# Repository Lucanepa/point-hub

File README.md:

# @openvolley/ledbox-bridge

Mirrors an OpenVolley live match onto a **Tech4Sport LedBox** LED scoreboard.

```
 eScoresheet (Scoreboard)                 LedBox bridge (this service)            Tech4Sport LedBox
        │  computes liveState                       │                                    │
        └── live-state-update (WS) ─▶  LAN relay ──▶  RelaySubscriber                     │
                                                     │  data.liveState                    │
                                                     ▼                                    │
                                            volleyballMapper ── SetSections ──▶ LedboxClient ──gzip/TCP:8889──▶ 📟
```

Small Node service, **no production dependencies** (uses Node 22's built-in global
`WebSocket` for the relay client and `node:net` for the LedBox). It subscribes to the
LAN relay, maps the live match state onto the LedBox `volleyball_matchscore` layout,
and pushes it over TCP with the documented gzip/JSON protocol.

The Point Hub apps (the tablet console, the desktop app for Linux, Windows and macOS) are
downloaded from https://lucanepa.github.io/point-hub/; how each channel is published:
[packaging/README.md](packaging/README.md).

### Runtime on the board

The board's own distro Node is far too old, so the runtime is a tarball install kept
outside the package manager:

    /opt/nodejs -> /opt/nodejs-22.23.2      # symlink; the previous version stays on disk
    /usr/local/bin/node -> /opt/nodejs/bin/node

Upgrading or rolling back is one flip of that symlink plus `systemctl restart
ledbox-bridge`, which is why the unit points at `/opt/nodejs/bin/node` rather than at a
versioned path or at `/usr/bin/node`.

**The board is armhf.** Its kernel is `aarch64` but the userland is 32-bit ARM, so it
needs the `linux-armv7l` tarball — an arm64 build unpacks perfectly and then refuses to
execute, which is a confusing way to find out.

**Node 22 is the last version this board can run.** There is no `linux-armv7l` build of
Node 24 at all; 32-bit ARM was dropped. Node 22 is supported until **2027-04-30**, and
getting past that needs a 64-bit userland on the board, not a newer tarball. Zero
production dependencies is what makes any of this cheap: there is nothing to rebuild
against a new runtime, so an upgrade is a download, a checksum and a symlink.

## Fields shown
points · team short names (in team colour) · sets won · timeouts (**T**) · substitutions (**S**) · serve indicator

## Configure
Copy `.env.example` → `.env`. Every var is optional for the appliance — an empty `.env`
boots a working board on the defaults below (`src/config.js` is the source of truth).

| Var | Default | Notes |
|---|---|---|
| `LEDBOX_HOST` | `172.24.1.1,192.168.5.1` | Comma-separated, tried in turn: the board's own AP, then the bench cable. Pinning ONE address loses the failover — leave it unset unless the board lives elsewhere. |
| `LEDBOX_PORT` | `8889` | |
| `CONTROL_PORT` | `8890` | The console. The QR on the panel and the hall guide point here. |
| `RELAY_URL` / `RELAY_HTTP_URL` | `ws://127.0.0.1:8080` / derived | OpenVolley relay for **Link** mode — only a fallback on the appliance: **Settings ▸ Scorer laptop address** wins (below). The match list (`/api/match/list`) is tried at the relay's own origin first (the standalone `backend/server.js` and the cloud serve HTTP and WS on one port), then on `:5173` of the same host (the desktop app, `frontend/server.js`). Set `RELAY_HTTP_URL` only to pin one URL. |
| `RELAY_DISCOVERY` | `own` | When the configured address does not answer, look for the scorer laptop: one `GET :8080/api/server/status` per address of the networks the board **runs** (its own address ends in `.1` — its Wi-Fi `172.24.1.x` and the bench cable `192.168.5.x`), then `:5173/api/server/status` where 8080 is WS-only, at most 6 s, only on a match-list refresh. Finds both relay families: the standalone `backend/server.js` (`status: 'online'` on 8080) and the desktop app — Tauri, Electron, `frontend/server.js` (`running: true` on 5173). `all` = every private /24 the board is on (a hall network it is a guest on included); `0` = off. A laptop the search found is used for a link only when the operator links a match it listed (each listed match names its laptop, and `POST /api/link` must name a relay the board knows); the Link tab warns when the saved address was silent and another laptop is listing. |
| `BOARD_OPENVOLLEY` | off | `1` = this C0270 serves OpenVolley itself (`pointhub-openvolley.service`, below): the board follows the one **live** match on its own relay (`ws://127.0.0.1:8080`) by itself, every 3 s, as the Point Hub board does for its screen — never over a game scored on the console or a countdown. Written by `provisioning/setup-openvolley-web.sh`. |
| `TLS_CERT`, `TLS_KEY`, `HTTPS_PORT` | empty, empty, `8891` | Both paths set = an HTTPS listener alongside HTTP (wake lock, installable app). Written by `provisioning/setup-console-tls.sh`. |
| `DIRECTUS_URL`, `LIVE_PUBLISH_TOKEN` | empty | Live publishing to wiedisync, below. The same token lets the board fetch the **match sheet** of the game on it (Link tab ▸ This game: Game info + KSCW roster, for the scorer to read off into the eScoresheet) — only with live scoring on, only behind the scorer PIN, and never on a board with no PIN set, because the roster holds birthdates. The copy in `data/gamesheet.json` is deleted once the game is off the board or 3 h past kickoff. Needs the `board` audience in wiedisync's `scorer-roster.js`. |
| `DIRECTUS_URL` (schedule) | `https://directus.kscw.ch` when unset | Where the **season's home games** come from (`GET /api/schedule`, the console's "start from the schedule" list). A public, token-free read of `/items/games`, so it works without `LIVE_PUBLISH_TOKEN`. The board downloads every remaining home game whenever it has an uplink (at boot, every 30 min, retrying 1→5 min after a failure, and as soon as NTP syncs) and keeps them in `data/schedule.json`, so a hall with no uplink still gets the list — marked stale. No copy at all = a plain "type the names instead" message, never an error. |
| `SCHEDULE_HALLS` | empty (every hall) | Comma list of hall names, e.g. `KWI A,KWI B`: only games in those halls are offered (and prepared automatically). Case-insensitive. |
| `SCHEDULE_SYNC` | on | `0` = no background download and no automatic pre-match; the schedule is then only fetched when a console asks for it. |
| `UPLINK_WATCH` | on | Watch the board's internet and offer the **hall Wi-Fi login** (below). `0` = no background probe. `UPLINK_PROBE_URL` / `UPLINK_PORTAL_URL` point it at a fake portal for testing; they default to Android's `generate_204` and `https://login.pwlan.ch`. |
| `CABLE_TRUST`, `CABLE_ADDRESS`, `CABLE_SUBNET` | on, `192.168.5.1`, `192.168.5.0/24` | **A tablet on the cable is never asked for the scorer PIN** (owner decision 2026-10-22: the cable is a direct, physical connection). A request that arrived on `CABLE_ADDRESS` (the board's eth0) from an address inside `CABLE_SUBNET` (the board itself excluded) passes every PIN gate, on http and https alike, is never counted by the brute-force lock-out, and is told so: `/api/status` answers it `pinRequired:false, pinTrust:"cable"`, `/api/settings` `pinSet:false` (so the tablet app's start-up PIN screen stays down), with `pinConfigured` saying whether the board has a PIN at all. Decided from the TCP connection only — no header, query or `X-Forwarded-For` counts. Everyone else (the board's Wi-Fi `172.24.1.x`, the hall uplink, the tailnet, loopback, a Wi-Fi client aiming at `192.168.5.1`) is gated as before. `CABLE_TRUST=0` switches it off; a malformed address or subnet switches it off too and says so at boot. See `src/cableTrust.js`, `test/cable-trust-selftest.mjs`. |
| `STATE_DIR` | empty (the checkout) | Where everything the appliance **writes** lives: `settings.json` (the scorer PIN with it), `data/` (match history, the resume slot, logs, the schedule copy, the upload ledger, the hall-login stamp, the match-sheet copy) and the boot markers `.sport-switch` and `data/.running`. Empty keeps the paths every board has always used. A board with a **read-only root** sets it to a directory on its persistent data partition (e.g. `STATE_DIR=/data/ledbox`, absolute): on an overlay root anything written elsewhere is lost at the next power cut. Not covered by it, because they belong to the OS or the panel firmware: `/etc/NetworkManager/system-connections`, `/var/lib/tailscale`, the TLS cert dir, the fake-hwclock / timesyncd stamps, and the firmware's own `setting.ini` and `PANEL_OFF` under `/home/pi/ledbox` — a read-only root bind-mounts those itself. A state dir that cannot be written is logged at boot at error level; the board still scores, from memory. `firmware/ledbox-watchdog.sh` reads the same `STATE_DIR` from this `.env`. `test/state-dir-selftest.mjs` fails on any new write path until it is classified. |
| `LOG_LEVEL` | `info` | `debug` \| `info` \| `warn` \| `error`; `DEBUG=1` is shorthand for `debug`. |
| `MOCK` | off | `1` = in-process mock LedBox, no hardware. |
| `MATCH_ID` | — | Only the headless `src/bridge.js` needs it; the appliance picks matches in the UI. It is the match's **seed key** (`match_…`, the `id` in the relay's `/api/match/list`, also in the scorer's QR code) — the relay keys rooms by it. The scorer's local numeric match id receives nothing. |

`LEDBOX_LAYOUT` is read by the headless bridge only — the appliance takes its layouts from the
active sport (`src/sports.js`).

### Publishing the board to wiedisync (`/live`)
Optional. Set **both** of these and the appliance mirrors every score change to the
club's Directus, so members can follow the match at `wiedisync.kscw.ch/live`:

| Var | Value |
|---|---|
| `DIRECTUS_URL` | `https://directus.kscw.ch` (dev: `https://directus-dev.kscw.ch`) |
| `LIVE_PUBLISH_TOKEN` | static token of `ledbox-board@kscw.ch` — its policy can touch `live_scores` and nothing else |
| `LIVE_CHANNEL` | the board's own row. Unset: `kscw` on the club's first board (host `ledbox-c0270`, or a generic host name such as `raspberrypi`), the host name on any other board (`ledbox-court2` → `ledbox-court2`), so a second board on defaults never overwrites the first one's row. Set it explicitly on every board; it must match the channel the board's token is allowed to write. Never `game-…` (ignored, with a warning). |

Leave either blank and the publisher is a **no-op** — the board behaves exactly as
it does without it.

**Two rows when the game is known.** Every match goes to the board's own row, team A =
the LEFT side, exactly as before. When the board knows *which game* it is showing — started
from the schedule (the console's tap or the automatic pre-match), or a linked OpenVolley
match whose match number (`game_n`) is in the season copy — it also writes wiedisync's
per-game row `game-<games.id>`, the row the game modal's *Watch live* and the result
entry's prefill read (`src/liveFixture.js`):

| | board row (`LIVE_CHANNEL`) | game row (`game-<id>`) |
|---|---|---|
| team A | whoever stands on the left (swaps at every change of ends) | the schedule's **home** team, all match |
| `set_results` | by side, swapped with the ends | by team, home first |
| written | every change | from the first point (not the 0-0 pre-match), when the names on the board tell home from away |
| extra columns | — | `game_id`, `source: 'board:<channel>'` |

Who is home is read from the names on the board against the schedule's; when they fit both
ways, a board set up from the schedule (home on the left) goes by `ends_swapped`. When the
names fit neither way (retyped, or the next game already up) **no** game row is written:
a missing prefill is a nuisance, a swapped one is a wrong result sent to Volleymanager.
The finished match's `live_history` row stays on the board's channel and, when the game is
known, carries `game_id` and is home/away too (a Directus that refuses `game_id` gets the
row again without it).

- **Linked OpenVolley matches.** OpenVolley publishes to the LAN relay and its own cloud,
  never to wiedisync, so the board mirroring it is the only writer of that game row — once
  per change, like the board row. A linked match is never filed under the game the board was
  set up for before the link; only its own match number counts.
- **KSCW vs KSCW.** A derby is two `games` rows (one per team, `type` home / away). The
  season copy fetches `type: home` only, so the game is published once, under the **home**
  team's row id; the away team's copy gets nothing (wiedisync resolves the sibling).
- **Refused.** Until wiedisync lets the board's token write `game-*` rows, Directus refuses
  them: the board says so once in the log, leaves that row alone for 30 min and keeps
  publishing its own row as before. A row nobody has written yet answers a PATCH with 403,
  so 403/404 mean "create it".
- **Phone live scoring** writes the same `game-<id>` rows; the board's write is
  unconditional, so while the board publishes a game, the board wins. Every failure inside it (outage, bad token, slow network) is
swallowed, so it can never affect scoring. These are deliberately distinct from
`RELAY_URL`, which is the LAN relay the board *subscribes* to.

A failed live write is retried with the latest score, backing off and bounded; a new
point during a backoff goes out after the normal debounce instead of waiting it out. A
4xx is not retried. A finished match's history row is resent only when it provably
never reached Directus, so a timeout can lose that row but never duplicate it.

⚠️ Prod and dev have **different** tokens, and the dev one is replaced by the
nightly prod clone. Collection, permissions and setup:
`wiedisync/src/modules/live/DIRECTUS-SETUP.md`.

The publisher sends the active sport, so the app renders the right board — the
sport is fixed at boot (switching it restarts the appliance). Note that
`BasketballSource` carries team fouls in `subs_a`/`subs_b`; `livePush` translates
that to explicit `fouls_a`/`fouls_b` on the wire.

## Test / run
```bash
# everything: source rules + every test/*-selftest.mjs (no network, no hardware; the panel
# driver tests — test:panel — need Linux for flock/pgrep and skip themselves elsewhere)
npm test

# unit test: mapper → client → mock LedBox (no deps, no hardware) — the on-Pi smoke test
npm run test:mapper

# integration tests: mock relay → bridge / appliance → mock LedBox (needs devDeps)
npm install && npm run test:relay

# end to end against the CURRENT OpenVolley relays (manual: needs an OpenVolley checkout with
# backend/ and frontend/ node_modules). Runs one match against each relay family on free ports —
# backend/server.js --local, frontend/server.js (the desktop Node relay, same core as Electron) and
# the Tauri relay (--server-only, when a build exists; skipped otherwise) — and drives the real
# appliance through the network search (the real /api/server/status), Settings, /api/matches and
# /api/link, asserts the panel at every step, exits 1 on any miss
npm run test:e2e                                   # OPENVOLLEY_DIR defaults to ../openvolley/escoresheet
E2E_RELAYS=backend,desktop npm run test:e2e        # a subset; OPENVOLLEY_TAURI_BIN = a Tauri build

# run for real against the built-in mock (no hardware):
MOCK=1 MATCH_ID=match_1759750000000_ab12cd RELAY_URL=ws://127.0.0.1:8080 node src/bridge.js

# run against a real LedBox (MATCH_ID = the seed key, see Configure):
MATCH_ID=match_1759750000000_ab12cd LEDBOX_HOST=172.24.1.1 node src/bridge.js
```

## OpenVolley on the board (C0270)
Score in OpenVolley on a **tablet or a phone**, with no laptop and no internet: the board serves
OpenVolley's own web app and relay (`frontend/server.js`, unchanged, HTTP **:5173**, WS **:8080**)
and follows the match by itself. Design and the per-device table:
[`docs/openvolley-link-DESIGN.md`](docs/openvolley-link-DESIGN.md). The Point Hub DIY board does
not need it: OpenVolley runs on its own screen.

| Device on `ledbox_C0270` (or the cable) | Do |
|---|---|
| any browser (phone, tablet, iPad, iPhone, PC) | open `http://172.24.1.1:5173` (cable: `http://192.168.5.1:5173`) |
| OpenVolley Android app | Options ▸ Server ▸ Change server ▸ Local ▸ `172.24.1.1` |
| PC with the OpenVolley desktop app | as before: its own relay, linked from the Link tab |

```bash
tools/build-openvolley-web.sh 3.0.20    # on a laptop: dist-openvolley/openvolley-web-3.0.20.tar.gz
./deploy-board.sh                       # ships it to /home/pi/openvolley-web/<version>, `current` flips
# once, on the board:
sudo bash ledbox-bridge/provisioning/setup-openvolley-web.sh            # --check
sudo bash ledbox-bridge/provisioning/setup-openvolley-web.sh --apply    # service + firewall defaults + BOARD_OPENVOLLEY=1
sudo bash ledbox-bridge/provisioning/install-firewall.sh                # opens 5173/8080 on the AP + cable
sudo bash ledbox-bridge/provisioning/install-firewall.sh --commit       # after a phone opened :5173
```
Each OpenVolley release: build its bundle and deploy again (the last 3 stay on the board; roll
back by pointing `current` at the old one and `sudo systemctl restart pointhub-openvolley`).
Tested by `OPENVOLLEY_WEB_DIR=<unpacked bundle> E2E_RELAYS=board npm run test:e2e`.

## Appliance — web control UI (manual + link)
Instead of the headless bridge, run the **appliance**: a phone-friendly control page
served by the Pi (`CONTROL_PORT`, default 8890) with two modes — **Manual** (drive the
board by hand: names, ±points, sets, timeouts, subs, serve, swap) and **Link** (list LAN
matches from the relay and mirror one live). Cloud/Supabase source is a stub.

- **Scorer laptop** — the relay Link mode reads from is the scorer's OpenVolley laptop, whose
  address changes from hall to hall. **Settings ▸ Scorer laptop address** takes `host[:port]`
  (`172.24.1.23`, `172.24.1.23:9000`; port 8080 when left out; a pasted `ws://…`/`http://…` URL is
  fine, `wss://host` for a relay on the internet), refused with the reason when malformed and kept
  with the other settings. **Check** saves it and asks the laptop for its matches. Empty (the
  default) = `RELAY_URL` if set, else the board itself, and when nothing answers the board searches
  its own Wi-Fi and cable for a laptop (`RELAY_DISCOVERY`, `src/relayAddress.js`). The Link tab
  names the laptop that answered — or the address it tried and why it failed — and a link
  subscribes to the relay that listed the match. A match is listed by the relay only once the
  scorer has synced it (today's relays also want the referee connection on).
- **End of a linked match** — when the scorer ends the match (`match_status: 'ended'` in the live
  state), the panel shows the result screen (winner, sets; the clock on a board without
  `kscw_result`); an undo of the end brings the score back. When the scorer deletes the match
  (`match-deleted`), the board unlinks (mode `idle`) and holds the clock — or keeps the result if
  it is already up — instead of freezing the last score. Relay `error` frames are logged.
- **Breaks of a linked match** — with one scorer at the OpenVolley laptop, the board runs the
  breaks itself, on the same break screen, clock and horn as a console tap: the scorer's timeout
  puts up **TIME OUT** with the calling team (the one whose timeout count went up), a set end the
  **INTERVAL** with the set score, each for the length in Settings ▸ Countdowns. Each is timed from
  the moment the board sees it, never from the laptop's `*_started_at`. The laptop's end takes it
  down — silently when the scorer stopped it early, with the horn when it lands within 3 s of the
  board's zero — and when that end never comes (a link drop), the board's own zero ends it. A
  timeout is on while `timeout_active` is; OpenVolley sets `set_interval_active` on the set_end
  frame only, so the next set's line-ups do not end the interval, and End interval, Start set, an
  undo or a rally in the new set do. A console tap wins: a skip stays skipped, a countdown the
  operator starts over it is theirs, and nothing starts over Show clock or with Settings ▸ Show on
  timeout / Show on set interval off. A match end ends any break before the result goes up.
  Indoor volleyball only (`sports.js` `linkBreaks`); beach, basketball and simple links are as
  before.
- **Live-state order** — OpenVolley numbers every live state it pushes (`_seq`, within the
  `_session` of one scoring page; a reload starts again at 1). A state older than the newest one
  the board has taken is dropped (`src/relaySubscriber.js`), so the relay's replay after a
  reconnect can neither roll the score back nor start a break twice.
- **Scorer PIN — mandatory** — the board's AP passphrase is on the panel, so a real boot requires a
  scorer PIN. A board that has none yet (every board on the day this shipped) refuses writes from
  its Wi-Fi with *"This board has no scorer PIN yet — set one in Settings before scoring."* and the
  console shows **Set a scorer PIN** in front of everything (PIN typed twice) until someone sets
  one — that one save needs no PIN. In the tablet app the console comes to the front by itself to
  do it; the app's own screens can only type a PIN. A tablet on the **cable** is never blocked
  (`CABLE_TRUST`) and only reminded. The PIN can be changed (with the current one), not removed.
  Lost PIN: on the board, remove `scorerPin` from `settings.json` (in `STATE_DIR`) and restart the
  bridge — it is back in the setup, and the next operator sets a new one. Keep the PIN in the vault
  and on the coaches' sheet, not on the public hall card.
- **Which board** — `/api/status.board` names the board beside `fontsize`: `id` (settings.json
  `boardId`, set on the board only and never through the API since tablets pair against it, else
  the hostname), `idSource`, `label` (`boardLabel`, e.g. "Court 2", else the id) and `caps`:
  `sports`, `panel` `{ width, height, source }` read from the firmware's `setting.ini` [DISPLAY]
  (192×64 when absent), `renderer` `{ kind: 'vendor' | 'openscore', version, device }` from the
  board's own Init reply (null before the first handshake). Nothing existing was renamed.

- **Undo** — one button beside the set strip takes back the last action, whatever it was
  (point, timeout, sub, swap, next set, reset), up to 30 steps; it reads what it will undo
  (`Undo · Point KSCW`) and the history log follows it. A second `+` for a team that has
  already won the set is refused instead of scoring (`set-closed`).
- **Schedule and pre-match** — the Link tab lists today's home games and the rest of the season
  (`GET /api/schedule?range=season`: `{ ok, fetchedAt, stale, today, upcoming:[{ date, games }] }`,
  served from the copy on the board's card). Tapping one sets it up behind the wall clock until
  the warm-up ends. With **Settings ▸ Prepare home games automatically** (on by default) the
  board does that tap itself 60 minutes before a game of its sport — once the clock is synced,
  never over a match in progress or a running countdown, never again for a game the scorer
  dismissed that day, and only when it is the one home game of its sport that day: with two or
  more it prepares none and the scorer picks one on the Link tab (`src/autoPrepare.js`).
- **Hall internet** — at a hall whose Wi-Fi has a login page (the KWI hall's `Free_WLAN_KTZH`,
  a Swisscom Public WLAN), live scoring stops until the board is logged in, and the board has no
  browser to do it in. **Settings ▸ Hall internet** does it from the console: the scorer's mobile
  number, then the SMS code; the board walks the portal itself (`src/hallLogin.js`) and stays
  logged in about 24 h. The Game tab shows a banner only while the login page is in the way. The
  number is asked for every time and never stored or logged — the scorer changes every match.
  `GET /api/uplink` → `{ status: online|portal|offline|checking, portal, ssid, validUntil,
  loggedInAt, step: idle|code }`; `POST /api/uplink/check`, `/api/uplink/login { phone }` →
  `{ ok, step:'code' }`, `/api/uplink/code { code }` → `{ ok, status:'online', validUntil }`
  (PIN-gated, always 200 with `{ ok:false, error }` in plain words on a refusal). Both login
  calls also carry the console's `epochMs`: the board has no RTC, and if its clock is behind the
  portal's (freshly renewed) certificate the HTTPS login fails, so it adopts the console's time —
  even mid-match — and tries once more. `/api/status` carries `uplink: { status, validUntil }`. The Wi-Fi itself is set up by
  `provisioning/setup-wlan1-client.sh --hall`, which also carries the DNS fix that network needs.
  When the scripted login cannot get through (the portal slow or changed), **Open the login page**
  shows the hall's own page on the tablet, fetched by the board (`src/portalProxy.js`, under
  `/hall-login/`), so it is still the board that logs in: `POST /api/uplink/portal` (PIN) opens it
  for that tablet for ten minutes, its scripts run sandboxed away from the console's storage, and
  its cookies stay on the board. An offline `/api/uplink` also names the Wi-Fi and says `why`.
- **Panel test** — **Diagnostics ▸ Panel test** is the volunteer's self-check of the LED hardware,
  on the glass: **Show test screen** puts up `kscw_test` (`layouts/36_kscw_test.xml`), which
  numbers the C0270's three 64×64 modules **1 | 2 | 3** from the left, frames each one in white and
  draws red, green, blue and white bars under each number. A dark module, a frame with a gap, a
  missing bar or numbers out of order point at that module or its ribbon. **Test horn** sounds the
  horn once — unless Settings ▸ Horn when a countdown ends is off, which it then says. Both are
  refused during a match (the scoreboard showing a started, unfinished match, or a linked match)
  and during a countdown. The test screen goes back to exactly what was there (the held clock,
  the crest, the scoreboard, the result) after 20 s, on **Back to normal now**, and the moment
  anything else wants the panel (a point, a countdown, Show clock…); a reconnect, the layout guard
  and the idle ticker each take down a test screen with no test behind it, so nothing can leave the
  panel on it. `POST /api/paneltest { action: 'start' | 'stop' | 'horn', seconds? }` (PIN; 409 with
  the reason when refused); `/api/status` carries `ledbox.test: { endsAt, remainingMs } | null`.
  The layout ships with `deploy-board.sh` like every `*_kscw_*.xml`. `npm run test:paneltest`.
- **Finished sets on the interval screen** — **Settings ▸ Display ▸ Finished sets on the interval
  screen** (off by default) puts each finished set (`25-21  23-25`, two to a line, the left team's
  score first) under the clock on the set-interval screen, in two new `kscw_break` sections,
  `hist1`/`hist2`. Only for matches scored on the board: a linked OpenVolley match sends no set
  scores. Written apart from the break screen itself, so a board whose `kscw_break` predates the
  two sections (layout not deployed, or the panel not restarted since) loses only these lines —
  refused once per connection and logged, the interval screen painted as before. Timeouts and the
  warm-up show none. A deliberately static line rather than a rotating carousel: the hall and the
  referees read the interval clock, and frames that change underneath it are motion for the camera.
  `npm run test:interval`.
- **Portrait works** — a phone held upright gets a stacked layout (left team on top) instead
  of a "rotate" wall; a dismissible tip still suggests landscape.
- **Theme** — **Settings ▸ Theme**: Light (the default), Dark, or E-ink — greyscale, paper white
  and ink black, for a phone courtside in full sun. Per screen, never on the board:
  `localStorage.theme`, shown as `<html data-theme="dark|eink">`, set by a boot script at the top
  of `web/index.html` before the first paint; `/logs` follows it. The looks are token sets on
  `:root`; e-ink carries what colour alone used to (which team, a limit, the chosen tab) as fill
  versus outline, dashes and underlines, and drops shadows and motion. `npm run test:theme`.
- **Inside the Android app** (`android/`, contract `android/BRIDGE.md`) — the app shows this console
  in a kiosk WebView. From app 1.1.0 it draws the header, the tab bar and the Game tab natively, and
  the console runs in *embed mode* under the app's tab bar for Link, History, Diagnostics and
  Settings, with the scorer PIN and the theme shared with the app (BRIDGE.md, "Native Game tab";
  `npm run test:embed`).
- **The tablet's app** — with `TLS_CERT`/`TLS_KEY` set (`provisioning/setup-console-tls.sh`),
  `/api/status` carries `httpsOrigin` (the cert's first DNS name + `HTTPS_PORT`; `null` without
  TLS or once the cert has expired), and a console opened on `http://172.24.1.1:8890` moves itself
  there when it can reach it — between matches, never mid-match (a *Switch* bar until then). From
  the https address Chrome offers **Install app** (`web/manifest.webmanifest`): full screen,
  landscape, screen kept awake from launch, no tap-to-start.
  - **Install it once with internet.** Chrome on Android builds the app (a WebAPK) through
    Google's servers; on the board's own Wi-Fi, which has none, the install can fail or fall back
    to a plain shortcut. Install while the tablet has internet *and* reaches the board by its
    tailnet name (Tailscale on the tablet, or the hall Wi-Fi when the board shares it), then launch
    it once on the board's Wi-Fi to check it opens full screen, landscape, and stays lit.
  - **The app is bound to that exact origin.** Renaming the tailnet node or changing
    `HTTPS_PORT` means uninstalling and installing it again.
  - **The first move to https asks for the PIN again.** Browser storage is per origin, so the
    https console starts without what the http one remembered (scorer PIN, keep-awake, the
    dismissed rotate tip). Once only.
  - **If the app opens on "The board didn't answer here"**, the tablet could not look the name up
    or reach it (Private DNS or Chrome Secure DNS set to a provider, mobile data carrying DNS, the
    tablet on another network). That page is `web/sw.js` — a service worker that caches nothing
    and only answers a page load that failed — and it links `http://172.24.1.1:8890`, which still
    works. A lapsed certificate shows Chrome's own warning page instead (no worker runs there):
    use the same plain address.
```bash
npm run appliance                 # open http://<pi-ip>:8890  (or http://openvolley:8890 over Tailscale)
MOCK=1 npm run appliance          # in-process mock LedBox, no hardware
npm run test:appliance            # API → source → mapper → mock LedBox integration test
```
Architecture and the remaining phases (cloud source, auth, persistence) are in
[`DESIGN-appliance.md`](./DESIGN-appliance.md).

## Logs — `/logs`
Everything the appliance does is recorded to one structured log: board writes and layout
switches, every scored action, source and relay lifecycle, settings changes, live-scoring
publishes, and the browser's own errors. Open **`http://<board-ip>:8890/logs`** (linked from
Settings ▸ Diagnostics) for a live tail with level/scope filters, search, download and a
runtime verbosity switch.

```bash
LOG_LEVEL=debug npm run appliance   # boot verbose (DEBUG=1 still works); also switchable at /logs
curl http://<board-ip>:8890/api/logs/export > board.jsonl  # the whole trail, for a bug report
journalctl -u ledbox-bridge -f                             # unchanged — everything still mirrors to stdout
```

Persisted to `data/logs/*.jsonl`, rotated at 5 MB × 3 files (**15 MB ceiling**, SD-card
friendly). The scorer PIN, the Directus token and any phone number are redacted before anything
is written.
Design notes: [`docs/logging-DESIGN.md`](./docs/logging-DESIGN.md).

## Livestream overlay — `/overlay` and `/api/overlay.json`
The board serves the score for a livestream, so nobody has to type it into the streaming software
a second time. Read-only and open (no PIN for a GET), and it carries nothing the club's public
`/live` page does not already show: team names, colours, sets, points, who serves, the finished
sets, and the countdown the panel is showing (time-out, interval, warm-up). Built from the same row
livePush publishes (`src/overlay.js` on top of `toRow`), so no player, referee or roster data can
reach it.

- **OBS** — Sources ▸ + ▸ *Browser*, URL `http://<board>:8890/overlay`, width **1920**, height
  **1080**. The page is transparent; only the scorebug in one corner is drawn. Options in the URL:
  `?corner=tl|tr|bl|br` (default `tl`), `?scale=1.5` (0.5–3), `?history=0` (hide the finished
  sets), `?preview=1` (a chequered backdrop, to judge it in an ordinary browser). The bug is hidden
  while the board has no match on it.
- **vMix** — Data Sources ▸ + ▸ *JSON*, URL `http://<board>:8890/api/overlay.json`, then bind a
  title's fields to its columns. One flat object, every key always present (blank or `0` when it
  does not apply):

  | Key | |
  |---|---|
  | `team_a`, `team_b` | the short code as the panel shows it (else the name), capitals |
  | `team_a_name`, `team_b_name`, `team_a_color`, `team_b_color` | full name; `#rrggbb` |
  | `points_a/b`, `sets_a/b`, `timeouts_a/b`, `fouls_a/b` | numbers (fouls: basketball) |
  | `serving` | `a`, `b` or empty |
  | `period`, `period_label` | `2`, `SET 2` (basketball `Q2`, `OT1`) |
  | `status` | `idle` (no match), `live`, `final` |
  | `set_scores`, `set1_a` … `set5_b` | `25-21  23-25`, and each set on its own |
  | `break`, `break_team`, `break_seconds`, `break_clock` | `TIME OUT`, `KSCW`, `23`, `0:23` |

  Teams are A and B as `/live` has them: on the board's own scoring, A is the team on the panel's
  left (a change of ends swaps them, as on the panel); a linked OpenVolley match keeps A fixed.
- **Live updates** — `/overlay` listens to `GET /api/overlay/stream` (Server-Sent Events: a frame on
  connect, then one per change) and polls the JSON every 3 s while the stream is down. At most 8
  streams at once (a 503 past that; the page then polls). Both endpoints answer cross-origin reads
  (`Access-Control-Allow-Origin: *`) — unlike every other read here — so a producer's own graphics
  page can use them. Overlay reads do not count as someone at the console: the panel's "Join WiFi /
  Open UI" QR codes are not hidden by a streaming PC left running.
- **Reaching the board** — the streaming laptop needs the internet, and the board's own Wi-Fi
  (`ledbox_C0270`) has none; a public hall Wi-Fi usually keeps its clients apart, so a laptop there
  rarely reaches the board either. What works: the board's **tailnet name** with Tailscale on the
  laptop; a **cable** to the board's ethernet (`http://192.168.5.1:8890/overlay`) while the laptop's
  Wi-Fi carries the stream; or the laptop on `ledbox_C0270` with its internet from a phone over
  **USB tethering**. A producer who cannot reach the board at all needs a page on kscw.ch reading
  the public `live_scores` row instead (the same read `/live` makes) — not built here.
- **Delay** — the overlay follows the board, which follows the scorer: a few seconds behind the
  rally. To line it up with the picture, delay the camera by the same amount (OBS: the camera's
  *Render Delay* filter, and the same *Sync Offset* on its audio).
- Where the stream goes (and who processes the players' images there) is the club's decision; the
  overlay itself adds team names and the score only. `npm run test:overlay`.

## Deploy on the Pi (systemd)
```bash
# on the Pi (reachable as `ssh openvolley`):
cd ~/ledbox-bridge
cp .env.example .env && nano .env        # optional — the defaults drive the board (see Configure)
sudo cp systemd/ledbox-bridge.service /etc/systemd/system/
sudo systemctl daemon-reload && sudo systemctl enable --now ledbox-bridge
journalctl -u ledbox-bridge -f
```

## Status / open items
- **Validated:** mapper + protocol + TCP client + relay subscriber, on the Pi 5 against
  mocks (`npm test`).
- **Wired (app side):** the Scoreboard now also pushes its computed live-state over the
  LAN relay as a `live-state-update` message (`Scoreboard.jsx`); `server.js` merges it
  into the match store and fans it out to subscribers, and the bridge consumes it.
  Verified with mocks — still needs a live end-to-end run with a real scoreboard + relay.
- **Pending (hardware):** confirm the real LedBox's `volleyball_matchscore` section
  names — especially `sub1`/`sub2` and the team-name fields — and upload a custom
  layout via TCP :12345 if they differ.

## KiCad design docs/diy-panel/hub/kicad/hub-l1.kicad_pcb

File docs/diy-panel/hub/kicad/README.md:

# Hub board L1 in KiCad

`build_pcb.py` turns `../layout.json` (the paper-checked positions from `../gen.mjs`) into
`hub-l1.kicad_pcb`: standard KiCad 9 footprints, a net on every pad, and a two-layer route from a
small grid router in the same script (0.3 mm tracks, 0.2 mm clearance, 0.6/0.3 mm vias). Nothing
is drawn by hand, so a change to the paper drawing is one `./make.sh` away from new Gerbers.

```bash
./make.sh        # layout.json → board → DRC (must be clean) → img/*.png → hub-l1-jlcpcb.zip
```

The board opens in KiCad as usual (`hub-l1.kicad_pro`). There is no schematic: the connections
are the table on page 3 of `../hub-level1.pdf`, and `build_pcb.py` (`net_for`, `RES_NETS`) is the
netlist.

## Ordering at JLCPCB

Upload `hub-l1-jlcpcb.zip`. Settings: 2 layers, 90 × 60 mm, 1.6 mm, quantity 5, HASL lead-free,
any colour, no assembly. Only PCB, no stencil.

## Parts to solder (all through-hole)

| Ref | Part | Qty |
|---|---|---|
| J1 | JST-XH socket, top entry, 6-pin (B6B-XH-A) | 1 |
| J2–J6, J8–J10 | JST-XH socket, 4-pin (B4B-XH-A) | 8 |
| J7, J11 | JST-XH socket, 2-pin (B2B-XH-A) | 2 |
| U1 | female header 2.54 mm, 1 × 10 and 2 × 10, 8.5 mm tall | 1 + 1 |
| U2 | female header 2.54 mm, 1 × 4, 8.5 mm tall | 1 |
| R1 / R2, R5 / R3, R4, R6, R7 | ¼ W axial: 10k / 150 / 47 | 1 / 2 / 4 |
| H1–H4 | M2.5 standoffs + screws | 4 |

Plus the matching pre-crimped JST-XH pigtails, and 4 straight male pins for the DS3231.

The JST-XH sockets go in with the latch side as printed on the silkscreen outline. The MCP23017
sits label side up (VCC on the square pad of the single row), the DS3231 chip side up on its four
pass-through pins.

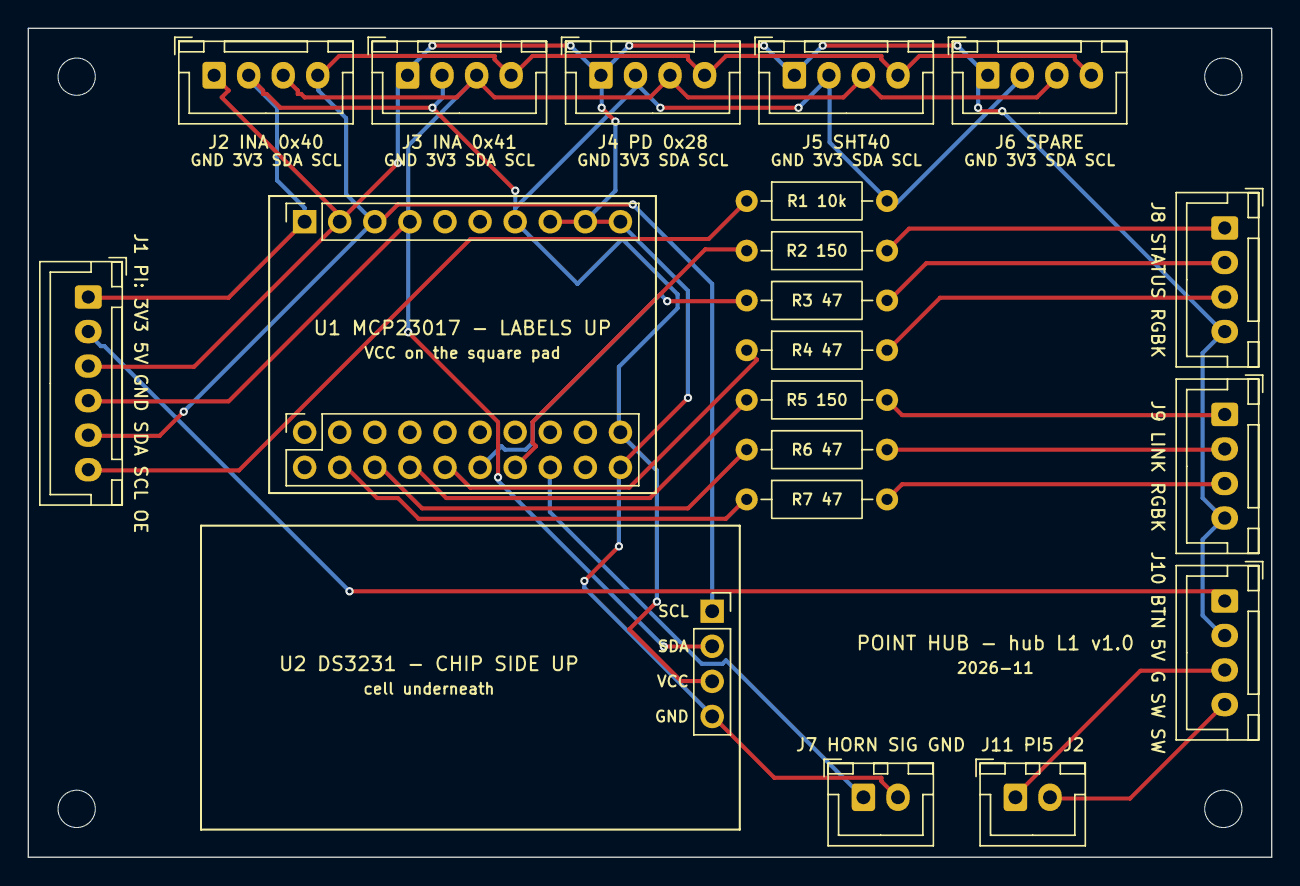
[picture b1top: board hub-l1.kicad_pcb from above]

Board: 2 copper layers, 90.0 x 60.0 mm, 25 parts (0 on the bottom side), 21 nets.

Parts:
H1, H2, H3, H4: M2.5; MountingHole_2.7mm_M2.5
J1: XH-6; JST_XH_B6B-XH-A_1x06_P2.50mm_Vertical
J2, J3, J4, J5, J6, J8, J9, J10: XH-4; JST_XH_B4B-XH-A_1x04_P2.50mm_Vertical
J7, J11: XH-2; JST_XH_B2B-XH-A_1x02_P2.50mm_Vertical
R1: 10k; R_Axial_DIN0207_L6.3mm_D2.5mm_P10.16mm_Horizontal
R2, R5: 150; R_Axial_DIN0207_L6.3mm_D2.5mm_P10.16mm_Horizontal
R3, R4, R6, R7: 47; R_Axial_DIN0207_L6.3mm_D2.5mm_P10.16mm_Horizontal
U1A: MCP23017 single row; PinSocket_1x10_P2.54mm_Vertical
U1B: MCP23017 ports; PinSocket_2x10_P2.54mm_Vertical
U2: DS3231 pass-through; PinSocket_1x04_P2.54mm_Vertical

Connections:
3V3: J1.1, J2.2, J3.2, J4.2, J5.2, J6.2, R1.2, U1A.1, U1A.7, U1B.19, U2.3
5V: J1.2, J10.1
BTN1: J10.3, J11.1
BTN2: J10.4, J11.2
GND: J1.3, J2.1, J3.1, J4.1, J5.1, J6.1, J7.2, J8.4, J9.4, J10.2, U1A.2, U1A.8, U1A.9, U1A.10, U1B.20, U2.4
GPA1: R2.1, U1B.14
GPA2: R3.1, U1B.12
GPA3: R4.1, U1B.10
GPA4: R5.1, U1B.8
GPA5: R6.1, U1B.6
GPA6: R7.1, U1B.4
HORN: J7.1, U1B.16
LK_B: J9.3, R7.2
LK_G: J9.2, R6.2
LK_R: J9.1, R5.2
OE: J1.6, R1.1
SCL: J1.5, J2.4, J3.4, J4.4, J5.4, J6.4, U1A.3, U2.1
SDA: J1.4, J2.3, J3.3, J4.3, J5.3, J6.3, U1A.4, U2.2
ST_B: J8.3, R4.2
ST_G: J8.2, R3.2
ST_R: J8.1, R2.2
